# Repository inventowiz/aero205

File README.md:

# aero205
Files used during air puck and hovercraft design during Aero205 W15.

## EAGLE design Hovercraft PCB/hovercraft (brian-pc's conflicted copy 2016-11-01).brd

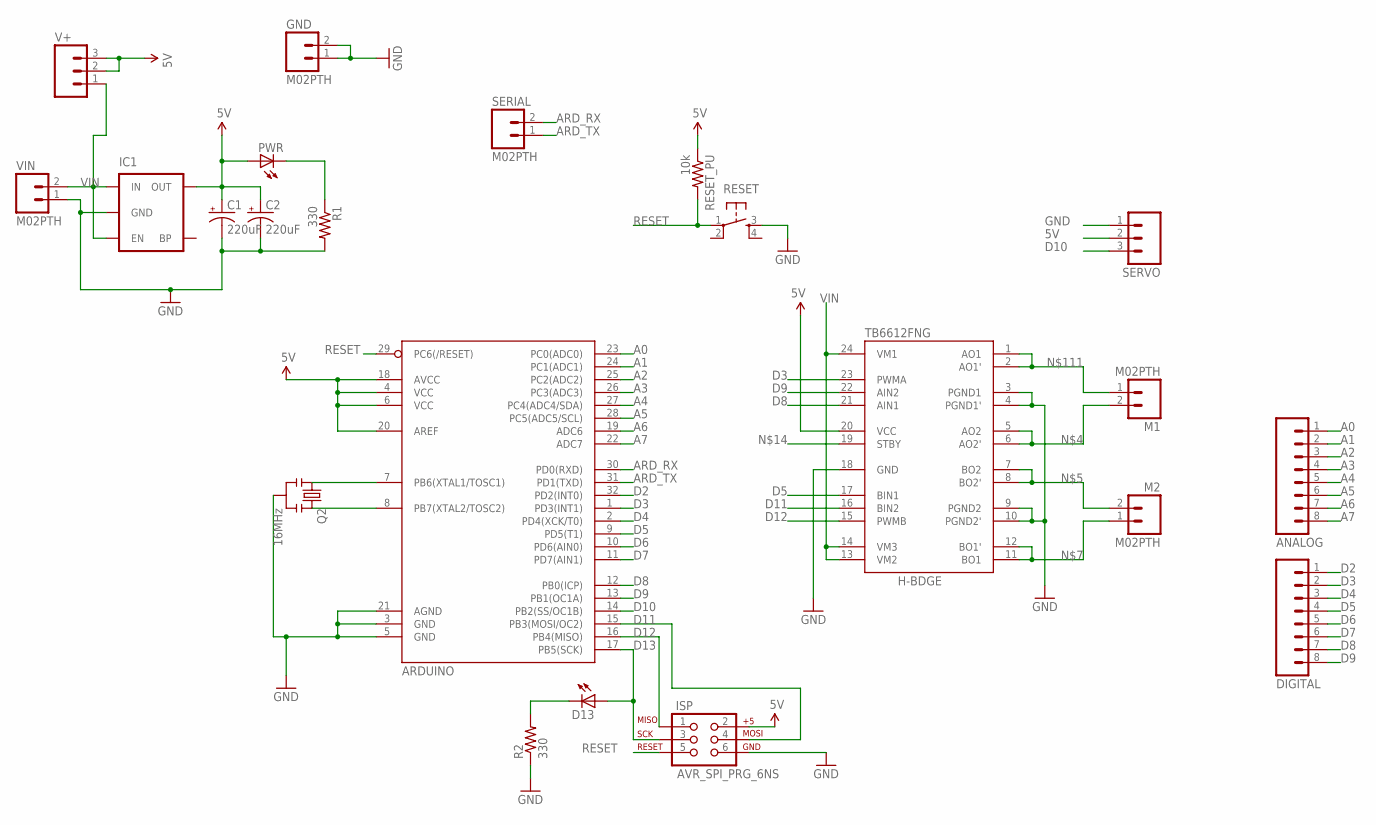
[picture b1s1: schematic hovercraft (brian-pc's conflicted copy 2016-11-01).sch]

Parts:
ANALOG: M08LOCK; 1X08_LOCK
ARDUINO: ATMEGA328_SMT; TQFP32-08
C1, C2: 220uF; CPOL-RADIAL-100UF-25V
D13: LEDCHIPLED_0805; CHIPLED_0805
DIGITAL: M08LOCK; 1X08_LOCK
GND: M02PTH; 1X02
H-BDGE: TB6612FNG; SSOP24
IC1: MIC52055V; SOT23-5
ISP: AVR_SPI_PRG_6NS; 2X3-NS
M1, M2: M02PTH; 1X02
PWR: LEDCHIPLED_0805; CHIPLED_0805
Q2: 16MHz; RESONATOR-SMD
R1, R2: 330; 0805
RESET: TAC_SWITCHSMD; TACTILE_SWITCH_SMD
RESET_PU: 10k; 0805
SERIAL: M02PTH; 1X02
SERVO: M03PTH; 1X03
V+: M03PTH; 1X03
VIN: M02PTH; 1X02

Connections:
5V: ARDUINO.4 (VCC), ARDUINO.6 (VCC), ARDUINO.18 (AVCC), ARDUINO.20 (AREF), C1.1 (+), C2.1 (+), H-BDGE.20 (VCC), IC1.5 (OUT), ISP.2, PWR.A, RESET_PU.1, SERVO.2, V+.2, V+.3
A0: ANALOG.1, ARDUINO.23 (PC0(ADC0))
A1: ANALOG.2, ARDUINO.24 (PC1(ADC1))
A2: ANALOG.3, ARDUINO.25 (PC2(ADC2))
A3: ANALOG.4, ARDUINO.26 (PC3(ADC3))
A4: ANALOG.5, ARDUINO.27 (PC4(ADC4/SDA))
A5: ANALOG.6, ARDUINO.28 (PC5(ADC5/SCL))
A6: ANALOG.7, ARDUINO.19 (ADC6)
A7: ANALOG.8, ARDUINO.22 (ADC7)
ARD_RX: ARDUINO.30 (PD0(RXD)), SERIAL.2
ARD_TX: ARDUINO.31 (PD1(TXD)), SERIAL.1
D2: ARDUINO.32 (PD2(INT0)), DIGITAL.1
D3: ARDUINO.1 (PD3(INT1)), DIGITAL.2, H-BDGE.23 (PWMA)
D4: ARDUINO.2 (PD4(XCK/T0)), DIGITAL.3
D5: ARDUINO.9 (PD5(T1)), DIGITAL.4, H-BDGE.17 (BIN1)
D6: ARDUINO.10 (PD6(AIN0)), DIGITAL.5
D7: ARDUINO.11 (PD7(AIN1)), DIGITAL.6
D8: ARDUINO.12 (PB0(ICP)), DIGITAL.7, H-BDGE.21 (AIN1)
D9: ARDUINO.13 (PB1(OC1A)), DIGITAL.8, H-BDGE.22 (AIN2)
D10: ARDUINO.14 (PB2(SS/OC1B)), SERVO.3
D11: ARDUINO.15 (PB3(MOSI/OC2)), H-BDGE.16 (BIN2), ISP.4
D12: ARDUINO.16 (PB4(MISO)), H-BDGE.15 (PWMB), ISP.1
D13: ARDUINO.17 (PB5(SCK)), D13.A, ISP.3
GND: ARDUINO.3 (GND), ARDUINO.5 (GND), ARDUINO.21 (AGND), C1.2 (-), C2.2 (-), GND.1, GND.2, H-BDGE.3 (PGND1), H-BDGE.4 (PGND1'), H-BDGE.9 (PGND2), H-BDGE.10 (PGND2'), H-BDGE.18 (GND), IC1.2 (GND), ISP.6, Q2.2, R1.2, R2.1, RESET.3, SERVO.1, VIN.1
unnamed: PWR.C, R1.1
unnamed: D13.C, R2.2
unnamed: H-BDGE.5 (AO2), H-BDGE.6 (AO2'), M1.2
unnamed: H-BDGE.7 (BO2), H-BDGE.8 (BO2'), M2.2
unnamed: H-BDGE.11 (BO1), H-BDGE.12 (BO1'), M2.1
unnamed: ARDUINO.7 (PB6(XTAL1/TOSC1)), Q2.1
unnamed: ARDUINO.8 (PB7(XTAL2/TOSC2)), Q2.3
unnamed: H-BDGE.1 (AO1), H-BDGE.2 (AO1'), M1.1
RESET: ARDUINO.29 (PC6(/RESET)), ISP.5, RESET.1, RESET_PU.2
VIN: H-BDGE.13 (VM2), H-BDGE.14 (VM3), H-BDGE.24 (VM1), IC1.1 (IN), IC1.3 (EN), V+.1, VIN.2

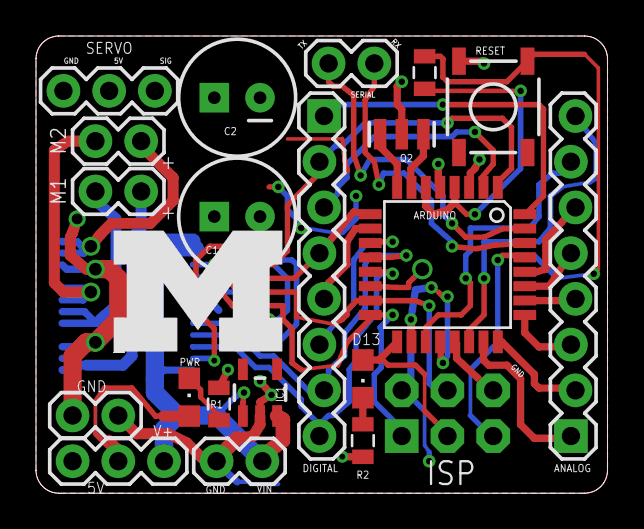
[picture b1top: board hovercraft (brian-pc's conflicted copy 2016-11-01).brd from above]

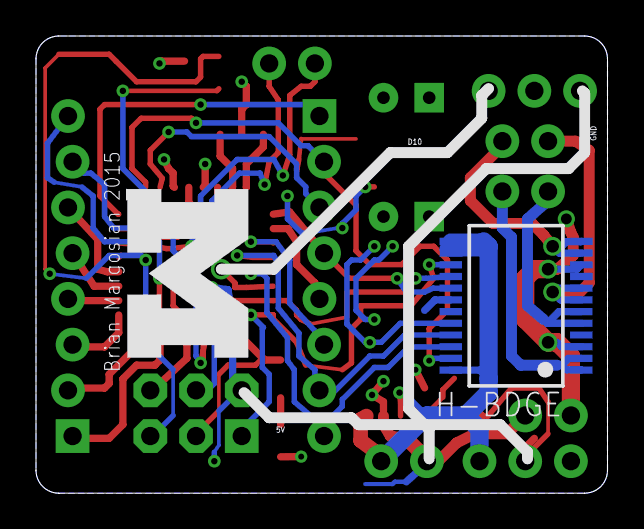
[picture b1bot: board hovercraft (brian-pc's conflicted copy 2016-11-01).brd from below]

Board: 2 copper layers, 31.8 x 25.4 mm, 24 parts (2 on the bottom side), 34 nets.

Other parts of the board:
U$1, U$2: BLOCKM

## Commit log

2015-04-11 Added code and PCB for class. During presentation
2016-11-11 Cleanup and sync of local files
2016-11-11 Fix broken code uploaded to git

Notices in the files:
parts and their libraries:
SparkFun-DigitalIC: Licensing: CC v3.0 Share-Alike You are welcome to use this library for commercial purposes.
